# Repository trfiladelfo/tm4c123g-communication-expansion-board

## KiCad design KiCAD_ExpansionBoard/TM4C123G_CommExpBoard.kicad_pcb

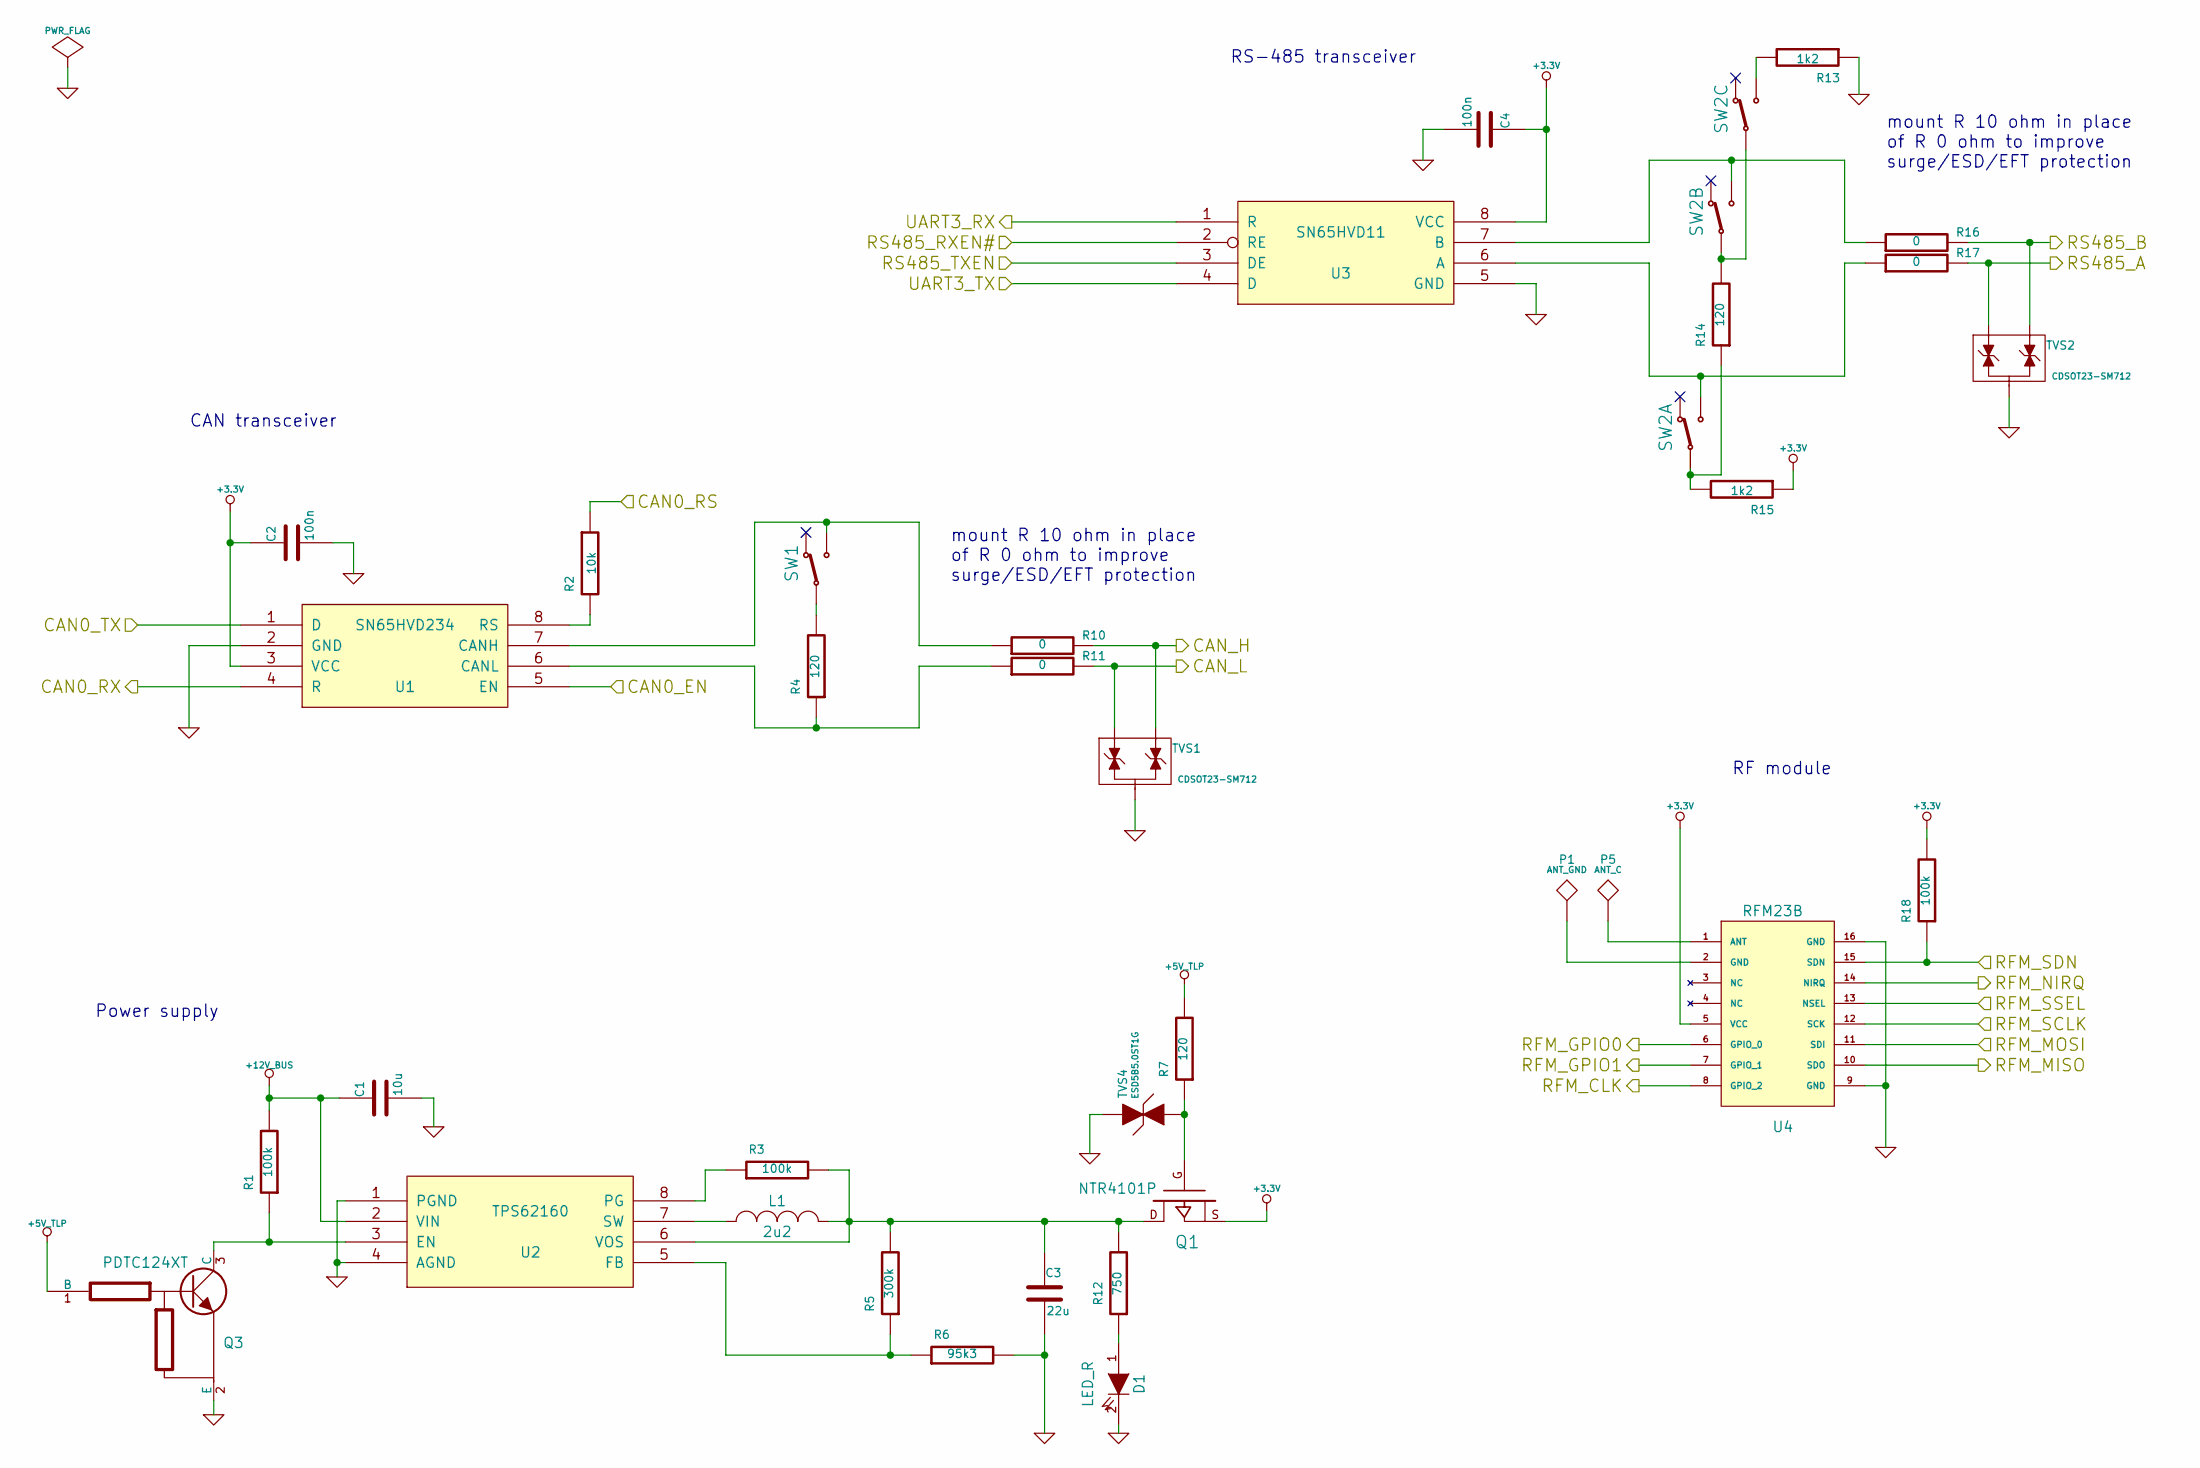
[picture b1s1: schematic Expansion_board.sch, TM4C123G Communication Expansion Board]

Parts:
C1: 10u
C2, C4: 100n
C3: 22u
D1: LED_R; SM_0603_MD
L1: 2u2
P1: ANT_GND
P5: ANT_C
Q1: NTR4101P
Q3: PDTC124XT; SOT23_MD
R1, R3, R18: 100k
R2: 10k
R4, R7, R14: 120
R5: 300k
R6: 95k3
R10, R11, R16, R17: 0
R12: 750
R13, R15: 1k2
SW1: SLIDE_SWITCH_SPDT
SW2: SLIDE_SWITCH_4PDT
TVS1, TVS2: CDSOT23-SM712
TVS4: ESD5B5.0ST1G; SOD-523_MD
U1: SN65HVD234; MODULE
U2: TPS62160; MODULE
U3: SN65HVD11; MODULE
U4: RFM23B

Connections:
+3.3V: C2.1, C4.1, Q1.S, R15.1, R18.2, U1.3 (VCC), U3.8 (VCC), U4.5 (VCC); also elsewhere on the board
+5V_TLP: Q3.1 (B), R7.2; also elsewhere on the board
+12V_BUS: C1.1, R1.2, U2.2 (VIN); also elsewhere on the board
/Expansion Board/CAN0_EN: U1.5 (EN); also elsewhere on the board
/Expansion Board/CAN0_RS: R2.1; also elsewhere on the board
/Expansion Board/CAN0_RX: U1.4 (R); also elsewhere on the board
/Expansion Board/CAN0_TX: U1.1 (D); also elsewhere on the board
/Expansion Board/CAN_H: R10.2, TVS1.2; also elsewhere on the board
/Expansion Board/CAN_L: R11.2, TVS1.1; also elsewhere on the board
/Expansion Board/RFM_CLK: U4.8 (GPIO_2); also elsewhere on the board
/Expansion Board/RFM_GPIO0: U4.6 (GPIO_0); also elsewhere on the board
/Expansion Board/RFM_MISO: U4.10 (SDO); also elsewhere on the board
/Expansion Board/RFM_MOSI: U4.11 (SDI); also elsewhere on the board
/Expansion Board/RFM_NIRQ: U4.14 (NIRQ); also elsewhere on the board
/Expansion Board/RFM_SCLK: U4.12 (SCK); also elsewhere on the board
/Expansion Board/RFM_SDN: R18.1, U4.15 (SDN); also elsewhere on the board
/Expansion Board/RFM_SSEL: U4.13 (NSEL); also elsewhere on the board
/Expansion Board/RS485_A: R17.2, TVS2.1; also elsewhere on the board
/Expansion Board/RS485_B: R16.2, TVS2.2; also elsewhere on the board
/Expansion Board/RS485_RXEN#: U3.2 (RE); also elsewhere on the board
/Expansion Board/RS485_TXEN: U3.3 (DE); also elsewhere on the board
/Expansion Board/UART3_RX: U3.1 (R); also elsewhere on the board
/Expansion Board/UART3_TX: U3.4 (D); also elsewhere on the board
/TM4C123G Connectors/RFM_GPIO0: U4.7 (GPIO_1); also elsewhere on the board
GND: C1.2, C2.2, C3.2, C4.2, D1.2 (K), Q3.2 (E), R6.2, R13.1, TVS1.3, TVS2.3, TVS4.1, U1.2 (GND), U2.1 (PGND), U2.4 (AGND), U3.5 (GND), U4.9 (GND), U4.16 (GND); also elsewhere on the board
unnamed: P1.1, U4.2 (GND)
unnamed: Q3.3 (C), R1.1, U2.3 (EN)
unnamed: R4.2, SW1.2 (COM)
unnamed: R17.1, SW2.3 (P2), U3.6 (A)
unnamed: R13.2, SW2.7 (P2)
unnamed: R5.1, R6.1, U2.5 (FB)
unnamed: R16.1, SW2.6 (P2), U3.7 (B)
unnamed: R4.1, R11.1, U1.6 (CANL)
unnamed: R10.1, SW1.3 (P2), U1.7 (CANH)
unnamed: R2.2, U1.8 (RS)
unnamed: P5.1, U4.1 (ANT)
unnamed: D1.1 (A), R12.1
unnamed: L1.1, U2.7 (SW)
unnamed: C3.1, L1.2, Q1.D, R3.2, R5.2, R12.2, U2.6 (VOS)
unnamed: Q1.G, R7.1, TVS4.2
unnamed: R14.1, R15.2, SW2.2 (COM)
unnamed: R3.1, U2.8 (PG)
unnamed: R14.2, SW2.5 (COM), SW2.8 (COM)

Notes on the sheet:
mount R 10 ohm in place of R 0 ohm to improve surge/ESD/EFT protection
RS-485 transceiver
CAN transceiver
Power supply
RF module

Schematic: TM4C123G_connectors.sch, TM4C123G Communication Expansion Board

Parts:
C5: 10n
C6, C7: 1n
J1: TI_BOOSTER_40_J1
J2: TI_BOOSTER_40_J2
J3: TI_BOOSTER_40_J3
J4: TI_BOOSTER_40_J4
P6: CAN
P7: UART1
P8: RS485
P9: UART2
P10: GPIO0
Q2: TSM3457; SOT-26_MD
R19: 10k
R20: 1k91
R21, R22: 22
R23, R24, R25, R26: 4k7
TVS3: SMCJ12CA; SMC

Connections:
+3.3V: J1.1, P7.6, P9.6, P10.1, R23.1, R24.1, R25.1, R26.1; also elsewhere on the board
+5V_TLP: J3.1; also elsewhere on the board
+12V_BUS: Q2.S, R19.1; also elsewhere on the board
/Expansion Board/CAN0_EN: J2.6; also elsewhere on the board
/Expansion Board/CAN0_RS: J2.7; also elsewhere on the board
/Expansion Board/CAN0_RX: J1.5; also elsewhere on the board
/Expansion Board/CAN0_TX: J1.6; also elsewhere on the board
/Expansion Board/CAN_H: P6.3; also elsewhere on the board
/Expansion Board/CAN_L: P6.2; also elsewhere on the board
/Expansion Board/RFM_CLK: J3.3; also elsewhere on the board
/Expansion Board/RFM_GPIO0: P10.6; also elsewhere on the board
/Expansion Board/RFM_MISO: J2.8; also elsewhere on the board
/Expansion Board/RFM_MOSI: J1.8; also elsewhere on the board
/Expansion Board/RFM_NIRQ: J2.3; also elsewhere on the board
/Expansion Board/RFM_SCLK: J2.10; also elsewhere on the board
/Expansion Board/RFM_SDN: J1.7; also elsewhere on the board
/Expansion Board/RFM_SSEL: J2.9; also elsewhere on the board
/Expansion Board/RS485_A: P8.2; also elsewhere on the board
/Expansion Board/RS485_B: P8.3; also elsewhere on the board
/Expansion Board/RS485_RXEN#: J3.5; also elsewhere on the board
/Expansion Board/RS485_TXEN: J3.6; also elsewhere on the board
/Expansion Board/UART3_RX: J4.6; also elsewhere on the board
/Expansion Board/UART3_TX: J4.7; also elsewhere on the board
/TM4C123G Connectors/+12V_BUS_UNP: P6.1, P8.1, Q2.D, TVS3.1
/TM4C123G Connectors/AIN0: C7.1, J3.9, R22.2
/TM4C123G Connectors/AIN1: C6.1, J3.8, R21.2
/TM4C123G Connectors/EXT_AIN0: P10.3, R22.1
/TM4C123G Connectors/EXT_AIN1: P10.4, R21.1
/TM4C123G Connectors/I2C0_SCL: J2.2, P10.8, R26.2
/TM4C123G Connectors/I2C0_SDA: J4.3, P10.7, R23.2
/TM4C123G Connectors/I2C1_SCL: J1.9, P10.10, R24.2
/TM4C123G Connectors/I2C1_SDA: J1.10, P10.9, R25.2
/TM4C123G Connectors/RFM_GPIO0: P10.5; also elsewhere on the board
/TM4C123G Connectors/UART1_CTS: J4.5, P7.4
/TM4C123G Connectors/UART1_RTS: J4.4, P7.1
/TM4C123G Connectors/UART1_RX: J1.3, P7.5
/TM4C123G Connectors/UART1_TX: J1.4, P7.3
/TM4C123G Connectors/UART2_RST: J3.4, P9.4
/TM4C123G Connectors/UART2_RX: J4.8, P9.5
/TM4C123G Connectors/UART2_TREQ: J1.2, P9.1
/TM4C123G Connectors/UART2_TX: J4.9, P9.3
/TM4C123G Connectors/V_AN_MONITOR: C5.1, J3.7, R19.2, R20.1
GND: C5.2, C6.2, C7.2, J2.1, J3.2, P6.4, P7.2, P8.4, P9.2, P10.2, Q2.G, R20.2, TVS3.2; also elsewhere on the board

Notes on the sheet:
Divider ratio=6.236
I2C: generic pull-up resistor
ADC input: generic anti-aliasing filter
Spare function 5x2 male header
RS-485 connector & power supply rail
CAN connector & power supply rail
UART1 3x2 male header
UART2 3x2 male header
4x Stackable 10 pin headers
Transient & reverse polarity protections of power supply rail

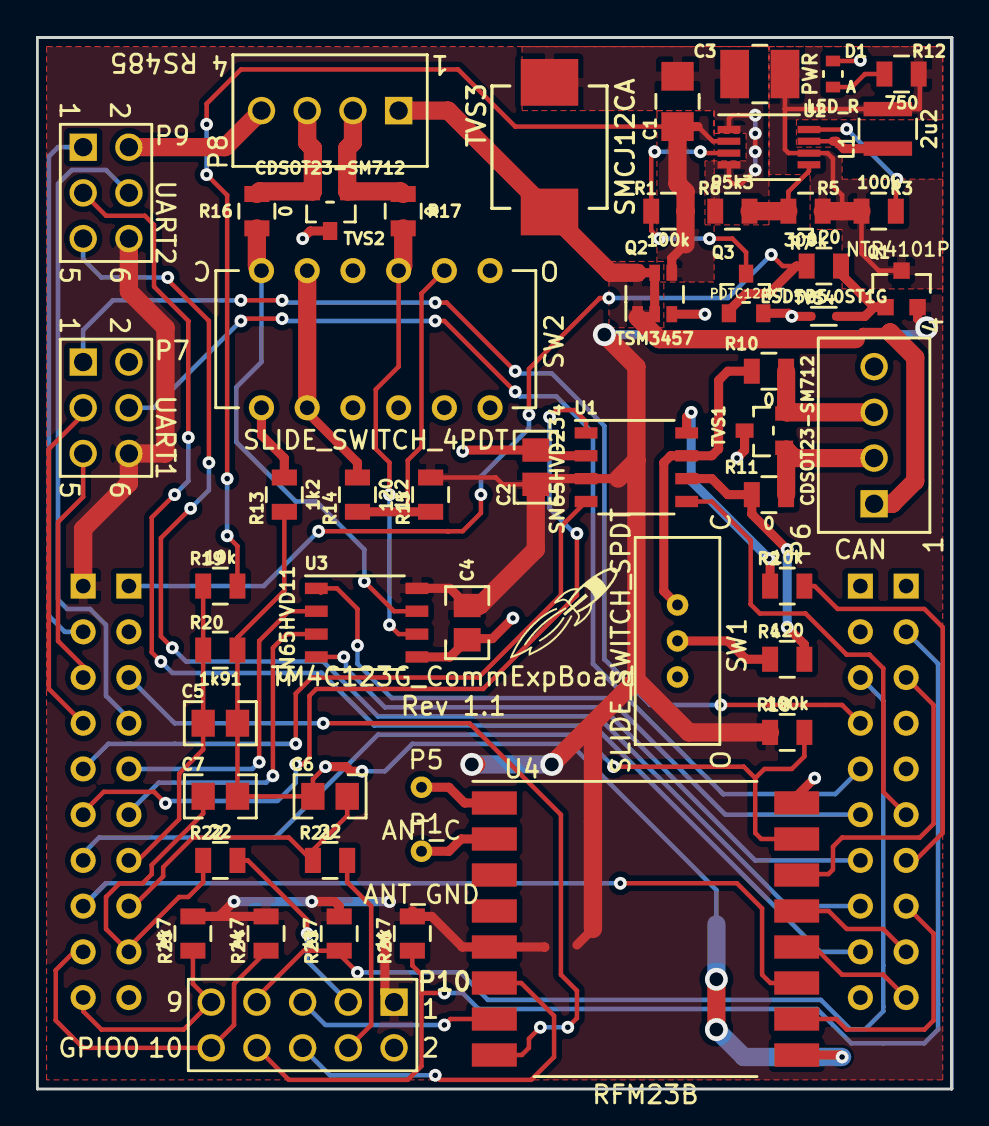
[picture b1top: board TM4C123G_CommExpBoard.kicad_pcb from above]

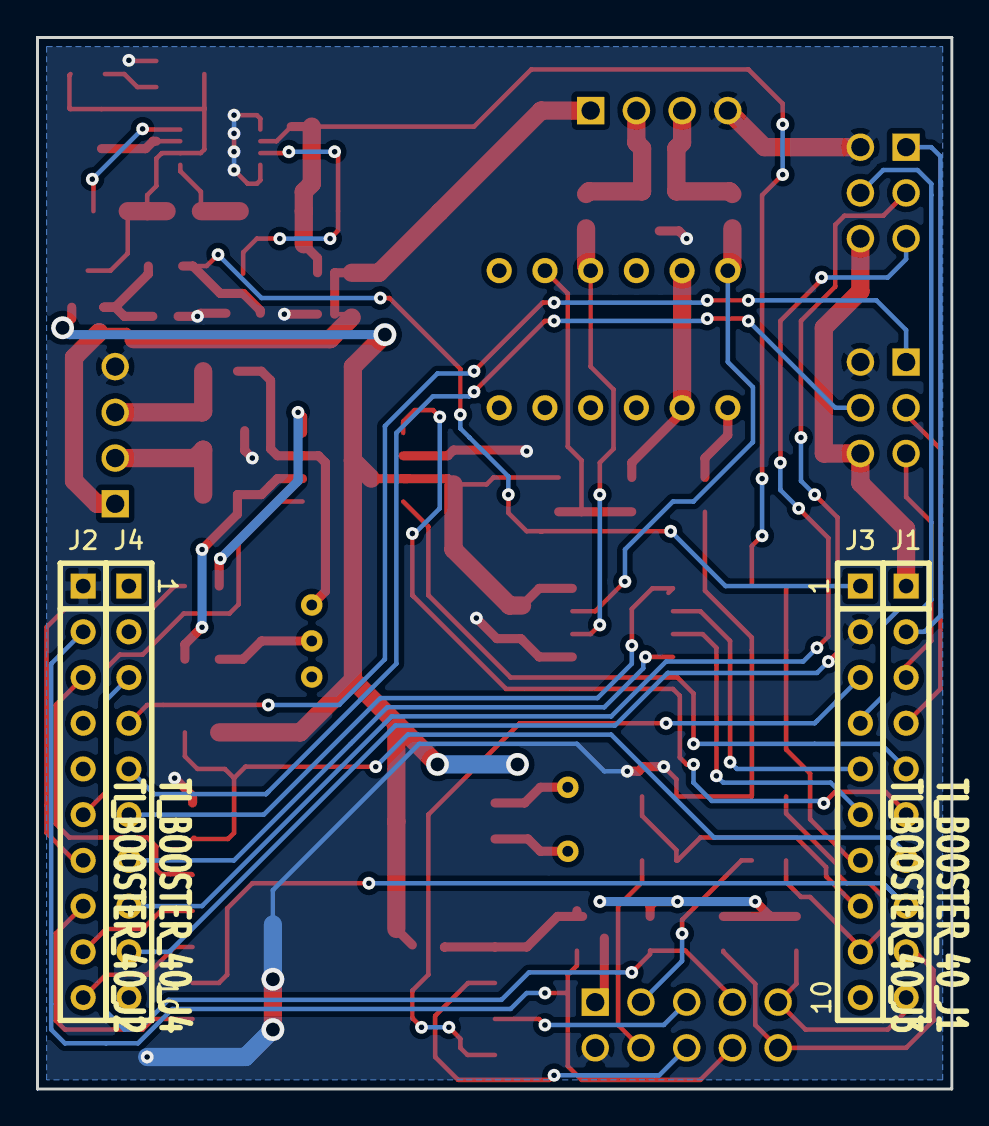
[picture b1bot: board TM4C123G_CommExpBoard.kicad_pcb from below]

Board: 2 copper layers, 50.8 x 58.4 mm, 58 parts (4 on the bottom side), 61 nets.

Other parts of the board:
G1: LOGO

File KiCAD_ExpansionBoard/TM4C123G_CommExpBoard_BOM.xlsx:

Valore | n° | Reference | Supplier 1 | Supplier 1 P/N | Manufacturer | Manufacturer P/N | Description | Supplier 2 | Supplier 2 P/N
1n | 2 | C6 C7 | Farnell | 1856477 | Multicomp | MCSH21B102K500CT | CONDENSATORE, 0805, X7R, 50V, 1NF
10n | 1 | C5 | Farnell | 1856485 | Multicomp | MCSH21B103K500CT | Â± 10%, X7R, 50V, 0805 [2012 Metric]
100n | 2 | C2 C4 | Farnell | 1856468 | Multicomp | MCSH21B104K250CT | CONDENSATORE, 0805, X7R, 25V, 100NF
10u | 1 | C1 | Farnell | 2112753 | MULTICOMP | MC1206X106K250CT | CAP, CERAMICA, 10UF, 25V, X5R, 1206
22u | 1 | C3 | Farnell | 2112725 | TDK | C3225X7R1C226K250AC | CONDENSATORE, 22UF, 16V, X7R, 1210
LED_R | 1 | D1 | Farnell | 1328308 | VISHAY | TLMS1000-GS08 | LED, 0603, RED, 4MCD, 628NM
TI_BOOSTER_40_J1 | 1 | J1 | Farnell | 1593464 | Multicomp | 2212S-10SG-85 | STACKABLE HEADER 10 PINS 2.54MM | Taydaelectronics | A-1053
TI_BOOSTER_40_J2 | 1 | J2 | Farnell | 1593464 | Multicomp | 2212S-10SG-85 | STACKABLE HEADER 10 PINS 2.54MM | Taydaelectronics | A-1053
TI_BOOSTER_40_J3 | 1 | J3 | Farnell | 1593464 | Multicomp | 2212S-10SG-85 | STACKABLE HEADER 10 PINS 2.54MM | Taydaelectronics | A-1053
TI_BOOSTER_40_J4 | 1 | J4 | Farnell | 1593464 | Multicomp | 2212S-10SG-85 | STACKABLE HEADER 10 PINS 2.54MM | Taydaelectronics | A-1053
2u2 | 1 | L1 | Farnell | 1612110 | TAIYO YUDEN | NR3015T2R2M | POWER INDUCTOR
CAN | 1 | P6 | Farnell | 3041414 | PHOENIX CONTACT | 1725672 | MORSETTIERA, 2,54MM, A 4 VIE, 20AWG
UART1 | 1 | P7 | Farnell | 1593440 | Multicomp | 2213S-06G | 3x2 male header
RS485 | 1 | P8 | Farnell | 3041414 | PHOENIX CONTACT | 1725672 | MORSETTIERA, 2,54MM, A 4 VIE, 20AWG
UART2 | 1 | P9 | Farnell | 1593440 | Multicomp | 2213S-06G | 3x2 male header
ANT_GND | 1 | P1
ANT_C | 1 | P5
EB_GPIO0 | 1 | P10 | Farnell | 1593442 | MULTICOMP | 2213S-10G | CONNECTOR, HEADER, THT, 2.54MM, 10WAY
TSM3457 | 1 | Q2 | Farnell | 1864583 | TAIWAN SEMICONDUCTOR | TSM3457CX6 | MOSFET, P CH, 30V, 5A, SOT26
PDTC124XT | 1 | Q3 | Farnell | 8737207 | NXP | PDTC124XT | TRANSISTOR, DIGITALE, SOT-23 NPN
NTR4101P | 1 | Q1 | Farnell | 1431303 | ON SEMICONDUCTOR | NTR4101PT1G | MOSFET, P, 20V, SOT-23
0 | 4 | R10 R11 R16 R17 | Farnell | 2073603 | MULTICOMP | MCMR08X000 PTL | RESISTORE, 0805, 0R, ANTI SOLFATAZIONE
22 | 2 | R21 R22 | Farnell | 1652962 | VISHAY DRALORIC | CRCW080522R0FKEA | RESISTOR, 22R0, 0.125W, 1%, 0805, SMD
120 | 3 | R4 R7 R14 | Farnell | 2073624 | MULTICOMP | MCMR08X1200FTL | RESISTOR, 0805, 120R, 1%, ANTI SULFUR
560 | 2 | R13 R15 | Farnell | 1469945 | VISHAY DRALORIC | CRCW0805560RFKEA | RESISTORE, 560R, 0.125W, 1%, 0805, SMD
750 | 1 | R12 | Farnell | 2057606 | PANASONIC | ERJ6ENF7500V | RESISTORE, 0805, 750R 1%, 0.125W
1k91 | 1 | R20 | Farnell | 2138942 | VISHAY DRALORIC | CRCW08051K91FKEA | RESISTORE, 0805, 1K91, 1%
4k7 | 4 | R23 R24 R25 R26 | Farnell | 2073779 | MULTICOMP | MCMR08X4701FTL | RESISTOR, 0805, 4K7, 1%, ANTI SULFUR
10k | 2 | R2 R19 | Farnell | 2073607 | MULTICOMP | MCMR08X1002FTL | RESISTOR, 0805, 10K, 1%, ANTI SULFUR
95k3 | 1 | R6 | Farnell | 1653045 | VISHAY DRALORIC | CRCW080595K3FKEA | RESISTOR, 0805, 95K3, 1%
100k | 3 | R1 R3 R18 | Farnell | 1652905 | VISHAY DRALORIC | CRCW0805100KFKTA | RESISTOR, 0805, 100K, 1%, THICK FILM CHIP RESISTOR
300k | 1 | R5 | Farnell | 2139063 | VISHAY DRALORIC | CRCW0805300KFKEA | RESISTORE, 0805, 300K, 1%
SLIDE_SWITCH_SPDT | 1 | SW1 | Farnell | 1123875 | ALPS | STSSS9121 | SLIDE SWITCH, SP 2 POS, VERT
SLIDE_SWITCH_4PDT | 1 | SW2 | Farnell | 1197659 | TE CONNECTIVITY | ASE4204 | INTERRUTTORE, 4PDT, 0,3A, 115VAC, THT
SMCJ12CA | 1 | TVS3 | Farnell | 1017847 | FAIRCHILD SEMICONDUCTOR | SMCJ12CA | DIODE, TVS, 12V, 1500W, SMC
ESD5B5.0ST1G | 1 | TVS4 | Farnell | 2317513 | ON SEMICONDUCTOR | ESD5B5.0ST1G | ESD PROTECTION DIODE, 5V, SOD-523-2
CDSOT23-SM712 | 2 | TVS1 TVS2 | Farnell | 1824869 | BOURNS | CDSOT23-SM712 | DIODE, UNIDIR TVS, 2 LINE, 7V&12V, SOT23
RFM23B | 1 | U4 | Idetron | RFM23B-433-S2 | HopeRF | RFM23B-433-S2 | The transceiver module is a complete RF receiver and transmitter, suited for ex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
SN65HVD234 | 1 | U1 | Farnell | 1212363 | Texas Instruments | SN65HVD234D | TRANSCEIVER CAN, 65HVD234, SOIC8
TPS62160 | 1 | U2 | Farnell | 2099930 | Texas Instruments | TPS62160DGKT | BUCK, 3V-17VIN, 2.25MHZ, 1A, ADJ, 8MSOP
SN65HVD11 | 1 | U3 | Farnell | 1100955 | Texas Instruments | SN65HVD11D | 3.3-V RS-485 TRANSCEIVERS

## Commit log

2014-06-09 Project loaded on Google code. The KiCAD schematic are still empty.
2014-06-09 Creation of project (sheets) structure and add some library schematic component (transceiver.lib, headers, etc.)
2014-07-01 Circuit board schematic complete! TODO: Update schematic according new received specifics: "note-expansionboard_20140623.txt"
2014-07-03 -Unito le due linee a 3.3V e riposizionato Q1 che ora va ad interrompere la linea di alimentazione a 3.3V dello switching quando è presente la +5V_TLP (USB). In serie al gate ho messo R8 da 120 ohm e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
    -Ho messo un NPN, Q3, che ha al suo interno un partitore da 22k + 47k; è pilotato dalla +5V_TLP ed ho messo R1 verso +12V_BUS che mantiene attivo lo switching a meno che non sia presente la +5V_TLP (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
    -Per la protezione dalle sovratensioni sulla +5V_TLP ho inserito, all'ingesso, TVS4 che è bidirezionale con tensione di lavoro a 5V e tensione di breakdown di 5.8V (min).
    -Rimosse tutte le resistenze di pu
2014-07-03 Lo schema elettrico è completo così come l'associazione di tutti i componenti ai footprint relativi. Definite le 2 dimensioni possibili dell'expansion board e la posizione definitiva dei connettori v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
2014-07-15 -Eliminata R7> con l-aggiunta di Q3 ora il pull down [ incorporato in esso, un-altro sprecher' solo corrente -Aumentate R1 e R18 a 100k -Modificata la connessione di SW2 per minimizzare la capacit' s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
2014-07-15 Creata le rev.03. Lo schema elettrico è completo; l'unico dubbio che si ha è sulla posizione del TVS4.
2014-07-15 -Aggiunta R7 in serie a monte del TVS4. Se non occorre, sostituire con una 0ohm.
2014-08-06 Eliminata R8 e collegata la piazzola P1 direttamente al pin 2 del RFM23B. Schema elettrico alla versione 0.3.3 Cretata la BOM definitiva in (TM4C123G_CommExpBoard_BOM.xlsx e TM4C123G_CommExpBoard.csv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
2014-08-06 Cambiato logo OSHW con il logo TI lauchpad
2014-08-06 Aggiornamento revisione su serigrafia scheda (0.3 invece di 1.0). La revisione della scheda sarà la stessa del file .pcbnew
2014-08-06 Modificato il nome di P10 GPIO0 al posto di EB_GPIO0 e schematico rinominato in rev.0.3.4; di conseguenza è stato rinominato il valore di P10 anche sul PCB. Aggiornate le serigrafie dei connettori su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
2014-08-07 Schema elettrico: variate le connessione del partitore di fail-safe-biasing. R13 è di pull-down ed R15 di pull-up, quindi sono connesse rispettivamente verso gnd e +3.3V. In precedenza erano scambiat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
2014-10-03 Aggiornamenti minori, aggiunta della cartella FW e documentazione TolhNet.
2014-10-04 - sostituiti i pad smd dell'antenna con due pad through hole; - ridotto il numero di vias sottostanti il modulo radio RFM23B e spostati i rimanenti in maniera da evitare la sovrapposizione con i vias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
    Aggiunta la cartella "PCB_fabrication" che contiene:
    - il file excel (BOM);
    - i file per le forature;
    - i file Gerber;
    - alcuni file .txt
2014-10-04 Final PCB revision, awaiting checking of Prof.
2014-11-12 moved P1 and P5 silkscreens near relative pads.
2014-11-26 Update of PCB and schematic to rev 1.1 (fixed old Q3 footprint in which pins 1 and 2 were flipped and relative nets). Build new v1.1 fabrication files.
2015-01-09 Prova da Linux Mint16
2015-01-09 Added Eclipse_Workspace from Mint16 VM
2015-01-09 Updated flags on compiler and linker template_TIVA_C project according to TolhNET FW
2015-01-09 loaded linker script file
2015-01-09 all flags are set-up! template_TIVA_C fully working!
2015-01-09 only one template for TIVA C is done and fully working!
2015-01-09 Developed and debugged GPIO example
2015-01-09 Added a new project: CAN_drv_example in order to develop drivers for CAN peripheral. It was derived by GPIO_example.
2015-01-12 Developed GPIO_eaxample project. Now the interrupt is working in either mode: - static allocation into interrupt vector table - dynamic allocation into interrupt vector table through function IntRegi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
    The PF0 pin, locked because it is a NMI pin, was unlocked.
2015-01-12 Updated GPIO_example project with UART transmission.
    Updated all project with proper Symbol definition (PART_TM4C123GH6PM). In past there was a wrong definition!
2015-01-12 Started to develop CAN_drv
2015-01-13 Developed CAN_drv: now there is some activity over the CAN bus.
2015-01-14 Development of CAN_drv_TX_example: It seems there is some trouble with countinuous call to CAN_IntHandler() but the CAN communication exist. Maybe due to lenght SW delay. In app_can.c is added a func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
2015-01-15 Added working CAN_drv_RX_example
2015-01-15 Developed working CAN_drv_RX_example and CAN_drv_TX_example!
2015-01-16 New verion of CAN_drv_TX_example. New logic to handle connection error. Now it's strongest regarding connection errors.
2015-01-16 New verion of CAN_drv_RX_example. New logic to handle connection error. Now it's strongest regarding connection errors. Still some trouble after about 5 minutes of working. Tx device seems it stop to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
2015-01-17 Added som debugging code into while infinite loop. now the communication do not stop. But...why?
2015-01-19 Interrupt disabling applied on (and only on) CAN_drv_TX_example. Now the interrupt is disabled into ISR and re-enabled into CAN BUS handling stuffs into main.c
2015-01-22 Working example showed to Professor. All went well. Interrupt disabling applied on (and only on) CAN_drv_TX_example. Now the interrupt is disabled into ISR and re-enabled into CAN BUS handling stuffs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
2015-01-23 Added multiple TX / RX version of FW
2015-01-23 Updated multiple TX code with a new function to transmit up to 256 byte of data
2015-01-24 Added a new project. It seems it work! Fix uartprintf into canhandler!
2015-01-25 minor changes: now multiTX not TX >4 packets. Probably ther's an error into "void app_can_SendMultipleMsg(const uint64_t* pui64_msg, const uint16_t msg_length)"
2015-01-25 multiTx seems working but UARTprintf work only first time it was called. Why?
2015-01-29 ligh modify to CAN_drv_RX_example
2015-04-02 Migrating wiki contents from Google Code
